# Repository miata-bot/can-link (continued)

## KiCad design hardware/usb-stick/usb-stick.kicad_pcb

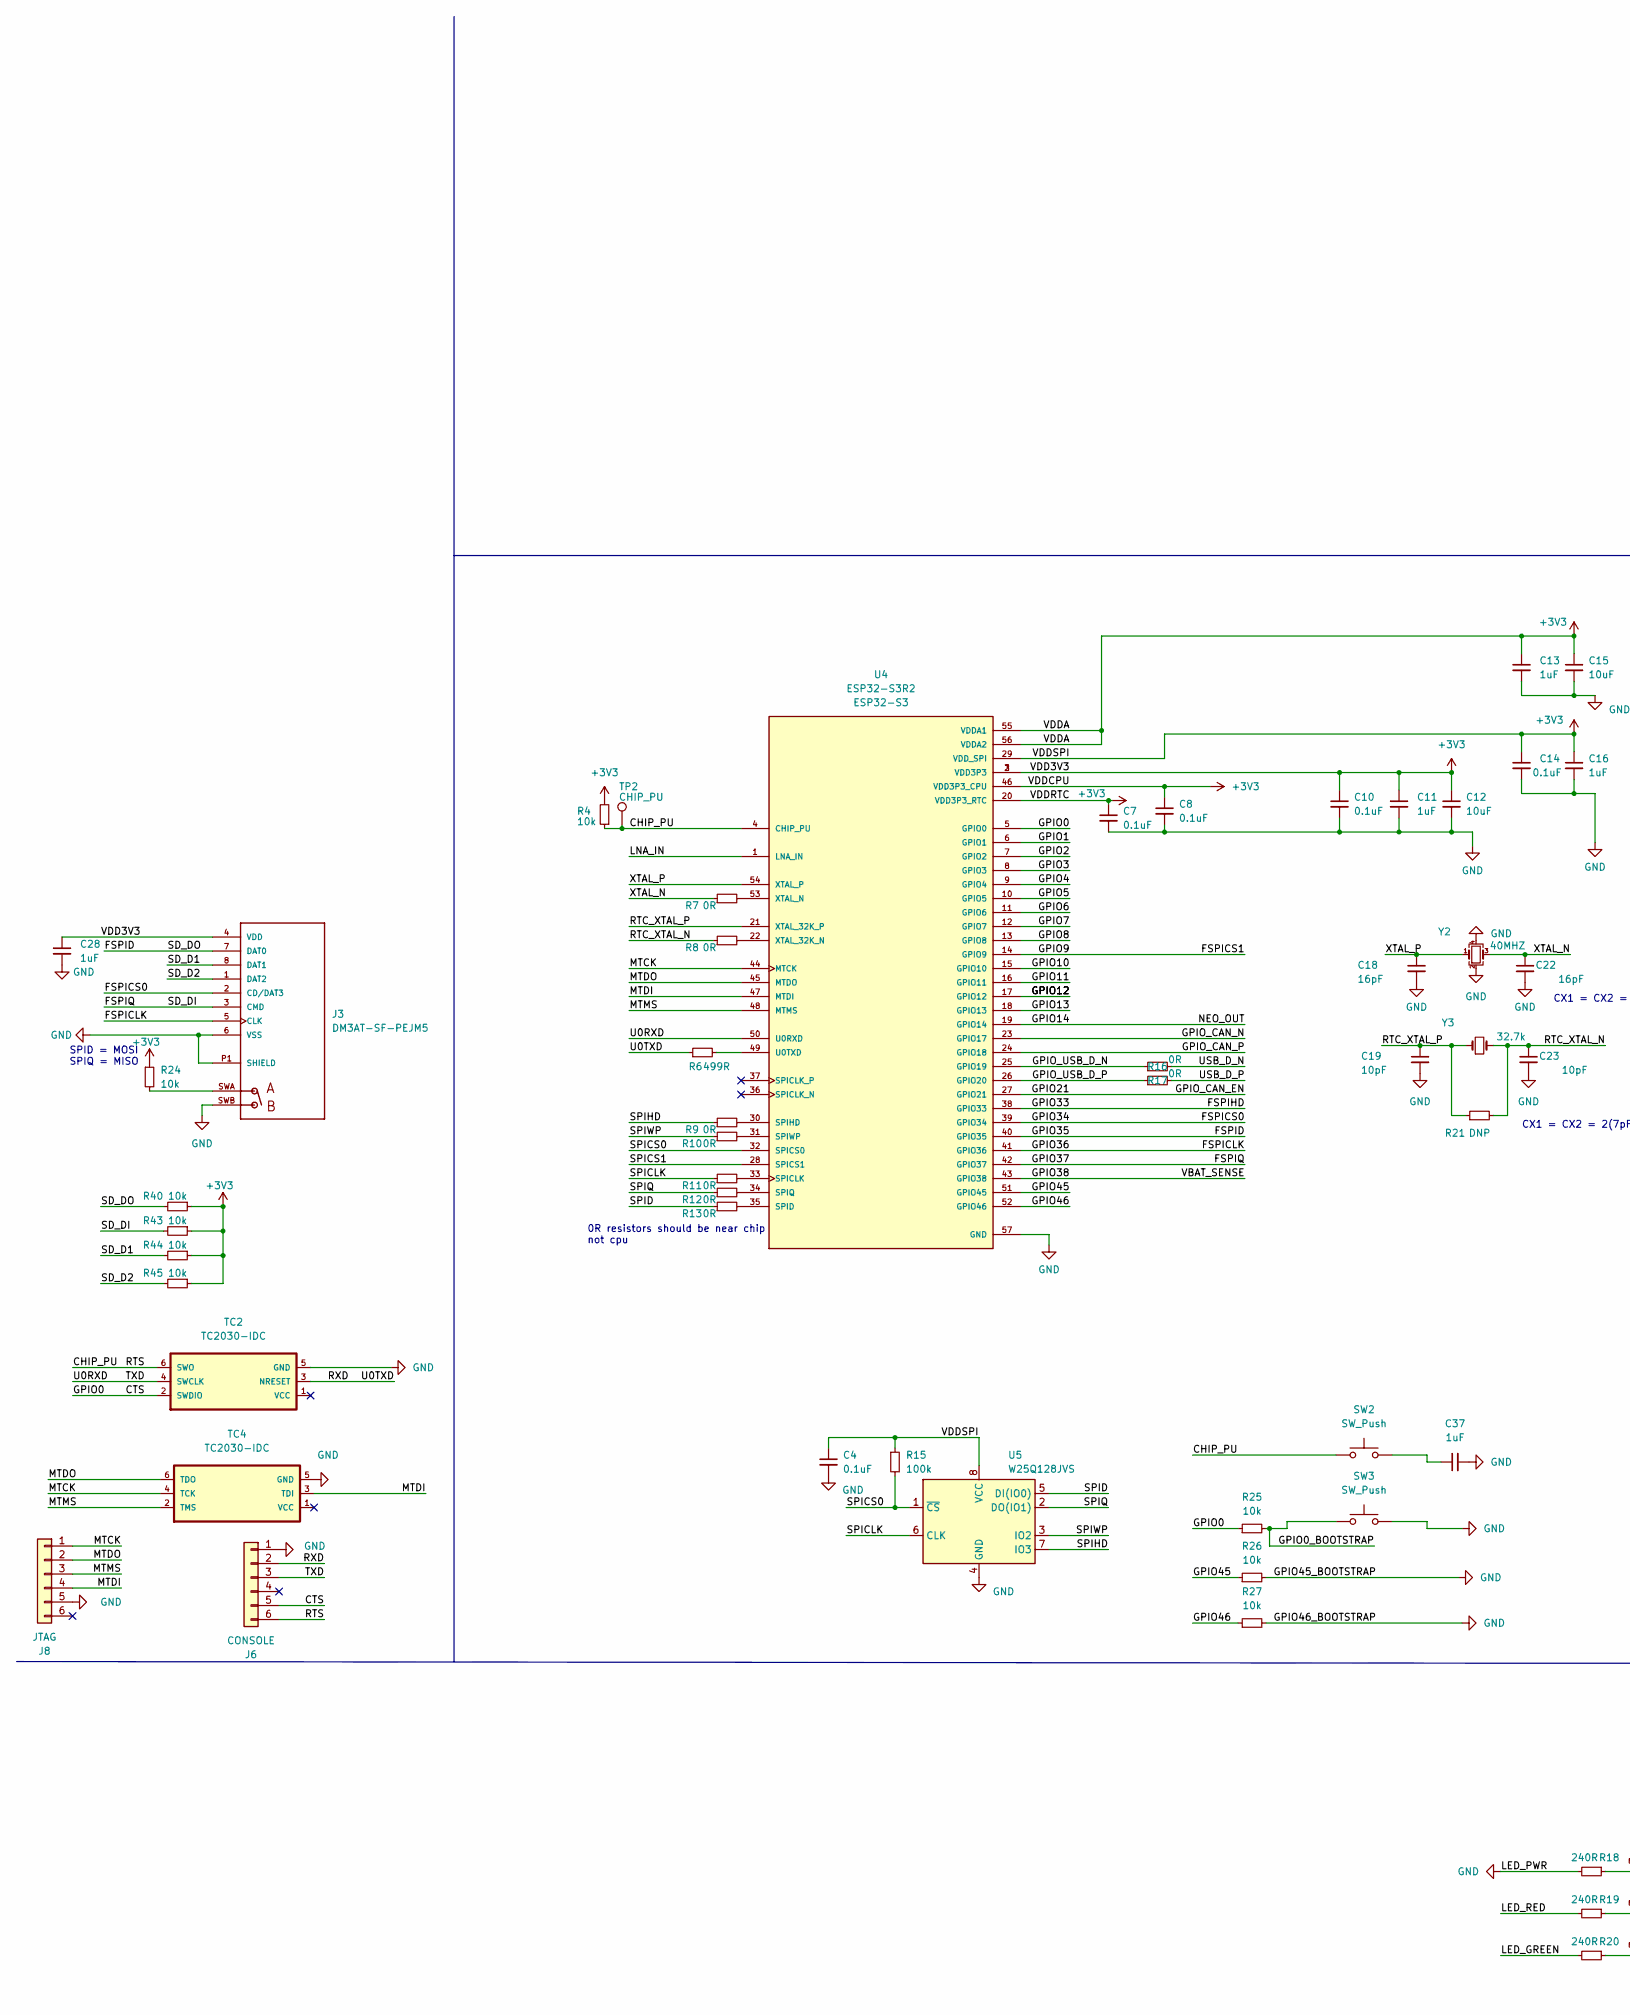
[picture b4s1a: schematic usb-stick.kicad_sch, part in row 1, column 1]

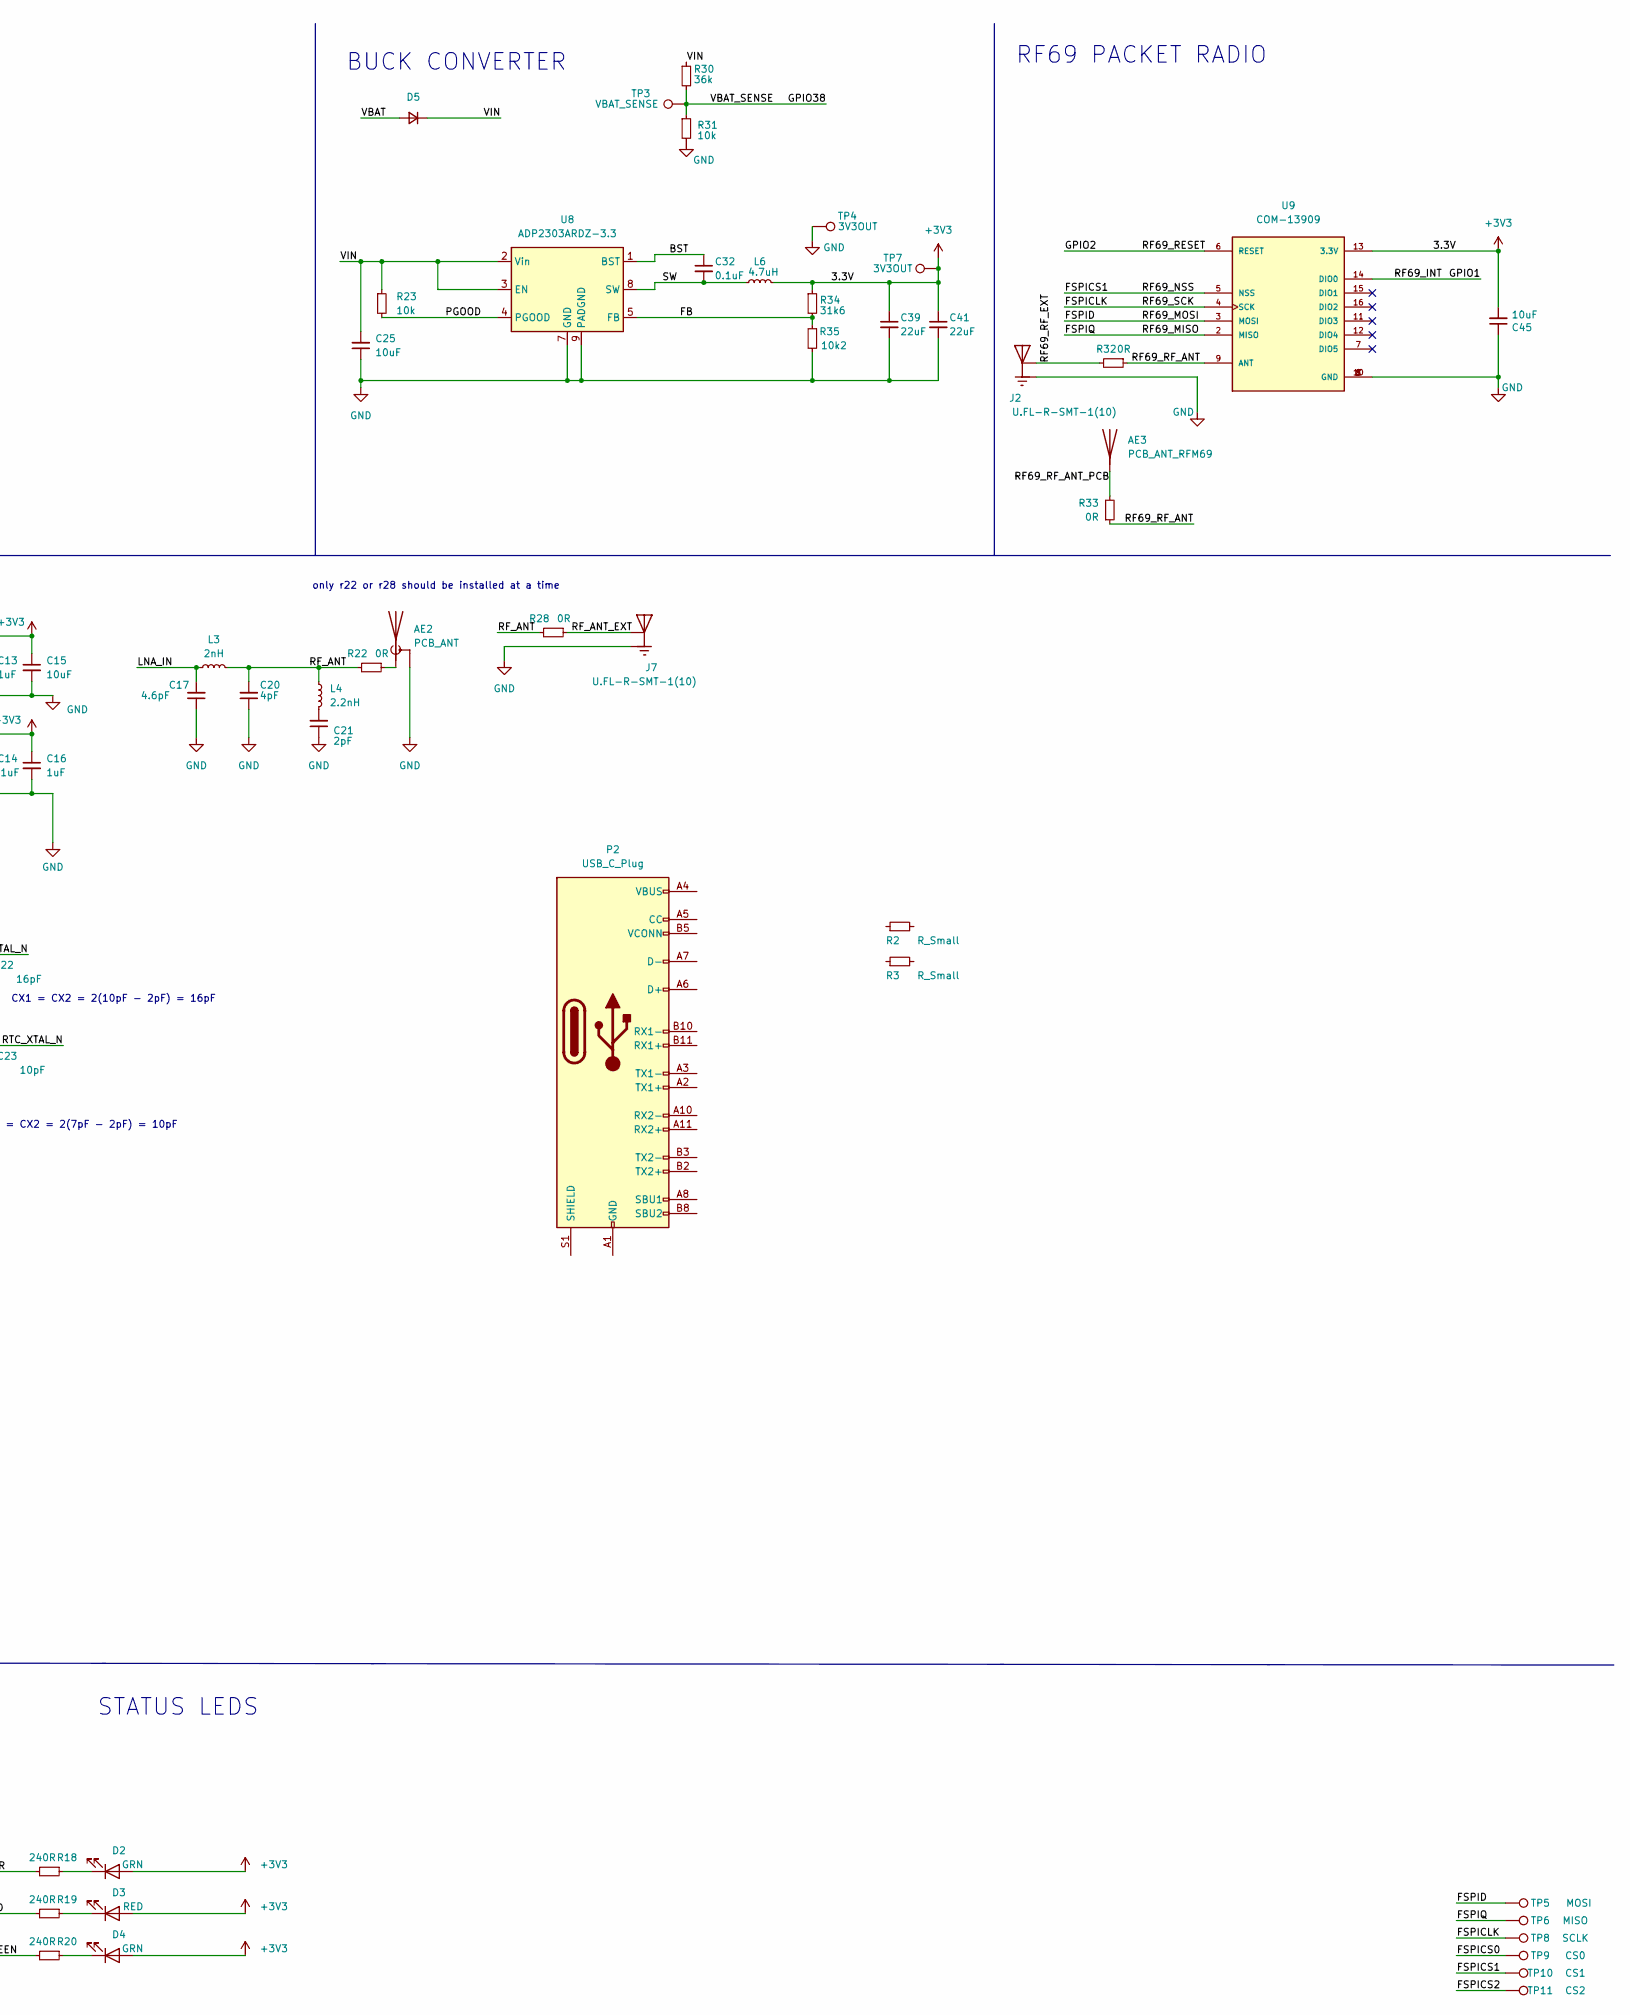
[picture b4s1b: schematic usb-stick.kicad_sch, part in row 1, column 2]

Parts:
AE2: PCB_ANT; Texas_SWRA117D_2.4GHz_Right
AE3: PCB_ANT_RFM69; Texas_SWRA416_868MHz_915MHz
C4, C7, C8, C10, C14: 0.1uF; C_0402_1005Metric; MPN C0805C104M3RAC7800
C11, C13, C16, C28, C37: 1uF; C_0402_1005Metric; MPN CGA2B1X7T0G105M050BC
C12, C15: 10uF; C_0402_1005Metric; MPN CL05X106MR5NUNC
C17: 4.6pF; C_0402_1005Metric; MPN TMK042CG4R6BD-W
C18, C22: 16pF; C_0402_1005Metric; MPN GCM1555C1H160JA16D
C19, C23: 10pF; C_0402_1005Metric; MPN C1005NP01H100D050BA
C20: 4pF; C_0402_1005Metric; MPN UMK105UJ040CV-F
C21: 2pF; C_0402_1005Metric; MPN UMK105CK020CVHF
C25, C45: 10uF; C_0805_2012Metric; MPN CL21A106KAFN3NE
C32: 0.1uF; C_0805_2012Metric; MPN LMK212SD104KG-T
C39, C41: 22uF; C_0805_2012Metric; MPN CL21A226MOQNNNE
D2, D4: GRN; LED_0603_1608Metric; MPN QBLP601-2IR4
D3: RED; LED_0603_1608Metric; MPN QBLP601-R35
D5: D_Small; D_SOD-123F; MPN CUHS15S30,H3F
J2, J7: U.FL-R-SMT-1(10); HRS_U.FL-R-SMT-1(10); MPN U.FL-R-SMT-1(10)
J3: DM3AT-SF-PEJM5; HRS_DM3AT-SF-PEJM5; MPN DM3AT-SF-PEJM5; LCSC C114218
J6: CONSOLE; PinHeader_1x06_P1.27mm_Vertical
J8: JTAG; PinHeader_1x06_P1.27mm_Vertical
L3: 2nH; L_0402_1005Metric; MPN LQG15HN2N0C02D
L4: 2.2nH; L_0402_1005Metric; MPN L-07C2N2SV6T
L6: 4.7uH; L_Bourns-SRN6028; MPN SRN6028-4R7M
P2: USB_C_Plug; USB_C_Plug_Molex_105444
R2, R3: R_Small; R_0402_1005Metric
R4, R24, R25, R26, R27, R31, R40, R43, R44, R45: 10k; R_0402_1005Metric; MPN RMCF0402JT10K0
R6: 499R; R_0402_1005Metric; MPN RMCF0402FT499R
R7, R8, R9, R10, R11, R12, R13, R16, R17, R22, R28, R32, R33: 0R; R_0402_1005Metric
R15: 100k; R_0402_1005Metric; MPN RNCF0402DTE100K
R18, R19, R20: 240R; R_0603_1608Metric; MPN RMCF0402JT240R
R21: DNP; R_0402_1005Metric; MPN RMCF2512ZT0R00
R23: 10k; R_0603_1608Metric; MPN RNCP0603FTD10K0
R30: 36k; R_0402_1005Metric; MPN RC0402FR-0736KL
R34: 31k6; R_0603_1608Metric; MPN RC0603FR-0731K6L
R35: 10k2; R_0603_1608Metric; MPN RNCF0603DTE10K2
SW2, SW3: SW_Push; SW_RS-032G05A3-SMRT; MPN RS032G05A3SMRT
TC2, TC4: TC2030-IDC; Tag-Connect_TC2030-IDC-NL_2x03_P1.27mm_Vertical
TP2: CHIP_PU; TestPoint_Pad_D1.0mm
TP3: VBAT_SENSE; TestPoint_Pad_D1.0mm
TP4, TP7: 3V3OUT; TestPoint_Pad_D1.0mm
TP5: MOSI; TestPoint_Pad_D1.0mm
TP6: MISO; TestPoint_Pad_D1.0mm
TP8: SCLK; TestPoint_Pad_D1.0mm
TP9: CS0; TestPoint_Pad_D1.0mm
TP10: CS1; TestPoint_Pad_D1.0mm
TP11: CS2; TestPoint_Pad_D1.0mm
U4: ESP32-S3R2; QFN-56; MPN ESP32-S3; LCSC C2913192
U5: W25Q128JVS; SOIC-8W_5.3x5.3mm_P1.27mm; MPN W25Q128JVS; LCSC C113767
U8: ADP2303ARDZ-3.3; SOIC-8-1EP_3.9x4.9mm_P1.27mm_EP2.29x3mm; MPN ADP2303ARDZ-3.3; LCSC C659152
U9: COM-13909; XCVR_RFM69HW; MPN COM-13909
Y2: 40MHZ; Crystal_SMD_3225-4Pin_3.2x2.5mm; MPN ECS-400-10-37B2-CKY-TR
Y3: 32.7k; Crystal_SMD_MicroCrystal_CC7V-T1A-2Pin_3.2x1.5mm; MPN ABS07-32.768KHZ-7-T

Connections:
+3V3: C4.1, C7.1, C8.1, C10.1, C11.1, C12.1, C13.1, C14.1, C15.1, C16.1, C28.1, C39.1, C41.1, C45.2, D2.2 (A), D3.2 (A), D4.2 (A), J3.4 (VDD), L6.2, R4.2, R15.1, R24.1, R34.1, R40.1, R43.1, R44.1, R45.1, TP7.1, U4.2 (VDD3P3), U4.3 (VDD3P3), U4.20 (VDD3P3_RTC), U4.29 (VDD_SPI), U4.46 (VDD3P3_CPU), U4.55 (VDDA1), U4.56 (VDDA2), U5.8 (VCC), U9.13 (3.3V)
/BST: C32.1, U8.1 (BST)
/CHIP_PU: J6.6, R4.1, SW2.1, TC2.6 (SWO), TP2.1, U4.4 (CHIP_PU)
/CTS: J6.5, R25.1, TC2.2 (SWDIO), U4.5 (GPIO0)
/FB: R34.2, R35.1, U8.5 (FB)
/FSPICLK: J3.5 (CLK), TP8.1, U4.41 (GPIO36), U9.4 (SCK)
/FSPICS0: J3.2 (CD/DAT3), TP9.1, U4.39 (GPIO34)
/FSPICS1: TP10.1, U4.14 (GPIO9), U9.5 (NSS)
/FSPICS2: TP11.1
/FSPID: J3.7 (DAT0), R40.2, TP5.1, U4.40 (GPIO35), U9.3 (MOSI)
/FSPIHD: U4.38 (GPIO33)
/FSPIQ: J3.3 (CMD), R43.2, TP6.1, U4.42 (GPIO37), U9.2 (MISO)
/GPIO0_BOOTSTRAP: R25.2, SW3.1
/GPIO1: U4.6 (GPIO1), U9.14 (DIO0)
/GPIO2: U4.7 (GPIO2), U9.6 (RESET)
/GPIO3: U4.8 (GPIO3)
/GPIO4: U4.9 (GPIO4)
/GPIO5: U4.10 (GPIO5)
/GPIO6: U4.11 (GPIO6)
/GPIO7: U4.12 (GPIO7)
/GPIO8: U4.13 (GPIO8)
/GPIO10: U4.15 (GPIO10)
/GPIO11: U4.16 (GPIO11)
/GPIO12: U4.17 (GPIO12)
/GPIO13: U4.18 (GPIO13)
/GPIO14: U4.19 (GPIO14)
/GPIO21: U4.27 (GPIO21)
/GPIO38: R30.2, R31.1, TP3.1, U4.43 (GPIO38)
/GPIO45: R26.1, U4.51 (GPIO45)
/GPIO46: R27.1, U4.52 (GPIO46)
/GPIO_CAN_N: U4.23 (GPIO17)
/GPIO_CAN_P: U4.24 (GPIO18)
/GPIO_USB_D_N: R16.1, U4.25 (GPIO19)
/GPIO_USB_D_P: R17.1, U4.26 (GPIO20)
/LED_GREEN: R20.2
/LED_RED: R19.2
/LNA_IN: C17.2, L3.1, U4.1 (LNA_IN)
/MTCK: J8.1, TC4.4 (TCK), U4.44 (MTCK)
/MTDI: J8.4, TC4.3 (TDI), U4.47 (MTDI)
/MTDO: J8.2, TC4.6 (TDO), U4.45 (MTDO)
/MTMS: J8.3, TC4.2 (TMS), U4.48 (MTMS)
/PGOOD: R23.2, U8.4 (PGOOD)
/RF69_RF_ANT: R32.1, R33.1, U9.9 (ANT)
/RF69_RF_ANT_PCB: AE3.1 (A), R33.2
/RF69_RF_EXT: J2.2, R32.2
/RF_ANT: C20.2, L3.2, L4.1, R22.2, R28.2
/RF_ANT_EXT: J7.2, R28.1
/RTC_XTAL_N: C23.1, R8.1, R21.2, Y3.2
/RTC_XTAL_P: C19.1, R21.1, U4.21 (XTAL_32K_P), Y3.1
/RXD: J6.2, R6.1, TC2.3 (NRESET)
/SD_D1: J3.8 (DAT1), R44.2
/SD_D2: J3.1 (DAT2), R45.2
/SPICLK: R11.1, U5.6 (CLK)
/SPICS0: R15.2, U4.32 (SPICS0), U5.1 (~CS)
/SPICS1: U4.28 (SPICS1)
/SPID: R13.1, U5.5 (DI(IO0))
/SPIHD: R9.1, U5.7 (IO3)
/SPIQ: R12.1, U5.2 (DO(IO1))
/SPIWP: R10.1, U5.3 (IO2)
/SW: C32.2, L6.1, U8.8 (SW)
/TXD: J6.3, TC2.4 (SWCLK), U4.50 (U0RXD)
/USB_D_N: R16.2
/USB_D_P: R17.2
/VBAT: D5.2 (A)
/VIN: C25.2, D5.1 (K), R23.1, R30.1, U8.2 (Vin), U8.3 (EN)
/XTAL_N: C22.1, R7.1, Y2.3
/XTAL_P: C18.1, U4.54 (XTAL_P), Y2.1
GND: AE2.2 (Shield), C4.2, C7.2, C8.2, C10.2, C11.2, C12.2, C13.2, C14.2, C15.2, C16.2, C17.1, C18.2, C19.2, C20.1, C21.1, C22.2, C23.2, C25.1, C28.2, C37.2, C39.2, C41.2, C45.1, J2.1, J2.3, J3.6 (VSS), J3.P1 (SHIELD), J3.SWB, J6.1, J7.1, J7.3, J8.5, R18.2, R26.2, R27.2, R31.2, R35.2, SW3.2, TC2.5 (GND), TC4.5 (GND), TP4.1, U4.57 (GND), U5.4 (GND), U8.7 (GND), U8.9 (PADGND), U9.1 (GND), U9.8 (GND), U9.10 (GND), Y2.2, Y2.4
unnamed: AE2.1 (A), R22.1
unnamed: C21.2, L4.2
unnamed: C37.1, SW2.2
unnamed: D2.1 (K), R18.1
unnamed: D3.1 (K), R19.1
unnamed: D4.1 (K), R20.1
unnamed: J3.SWA, R24.2
unnamed: P2.A1 (GND), P2.A12 (GND), P2.B1 (GND), P2.B12 (GND)
unnamed: P2.A4 (VBUS), P2.A9 (VBUS), P2.B4 (VBUS), P2.B9 (VBUS)
unnamed: R6.2, U4.49 (U0TXD)
unnamed: R7.2, U4.53 (XTAL_N)
unnamed: R8.2, U4.22 (XTAL_32K_N)
unnamed: R9.2, U4.30 (SPIHD)
unnamed: R10.2, U4.31 (SPIWP)
unnamed: R11.2, U4.33 (SPICLK)
unnamed: R12.2, U4.34 (SPIQ)
unnamed: R13.2, U4.35 (SPID)

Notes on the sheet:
CX1 = CX2 = 2(7pF - 2pF) = 10pF
only r22 or r28 should be installed at a time
0R resistors should be near chip not cpu
SPID = MOSI SPIQ = MISO
STATUS LEDS
BUCK CONVERTER
RF69 PACKET RADIO
CX1 = CX2 = 2(10pF - 2pF) = 16pF

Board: 4 copper layers, 94 parts (2 on the bottom side), 63 nets, no tracks yet.
